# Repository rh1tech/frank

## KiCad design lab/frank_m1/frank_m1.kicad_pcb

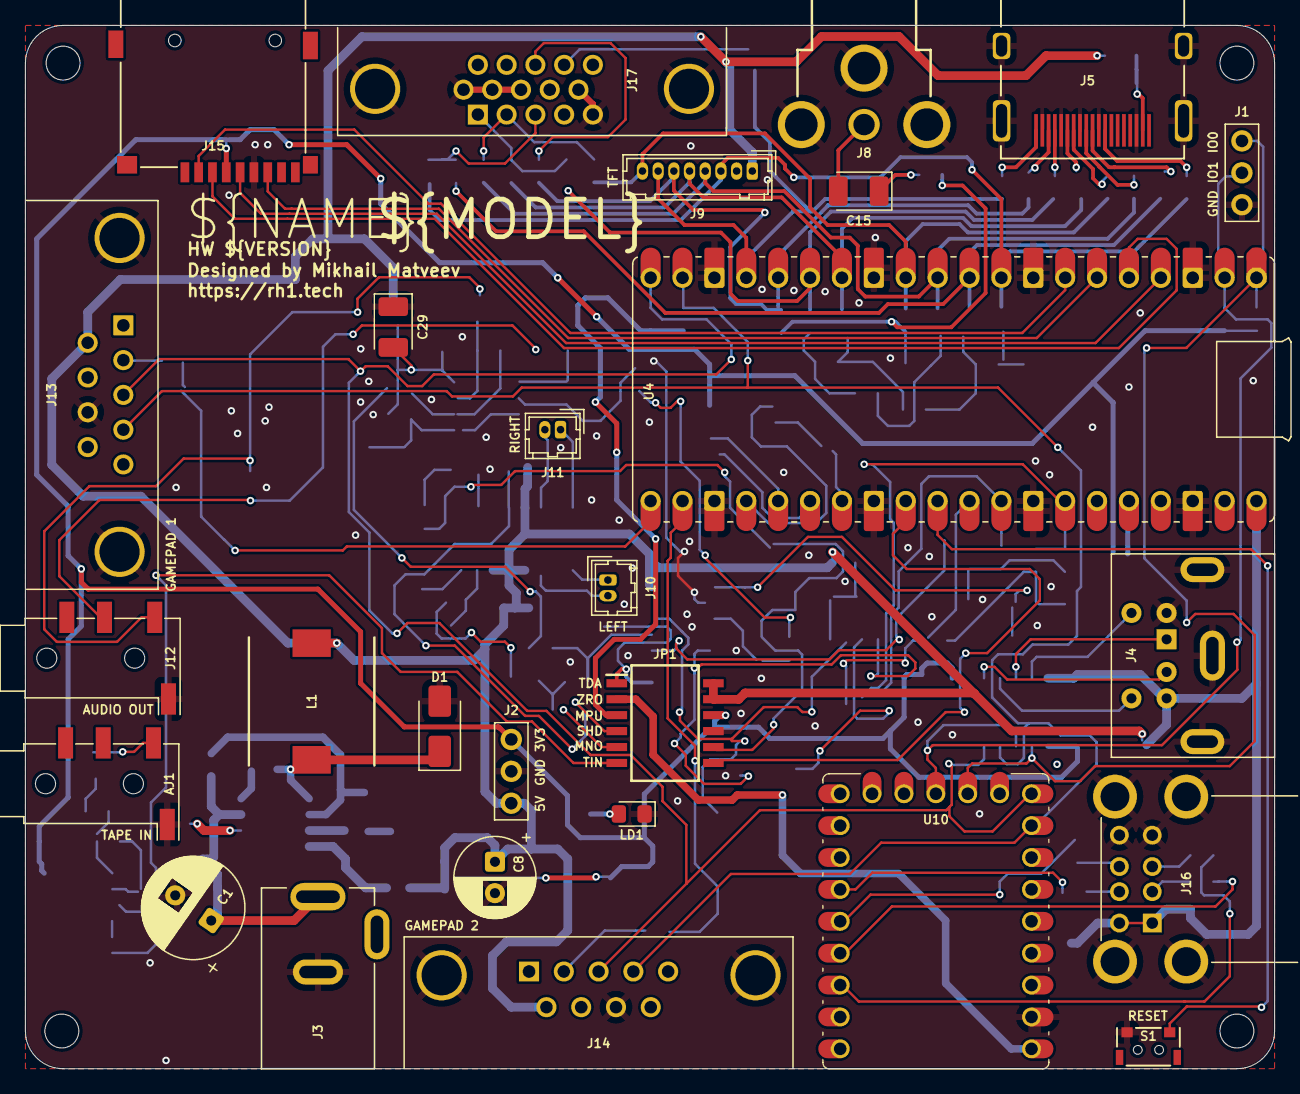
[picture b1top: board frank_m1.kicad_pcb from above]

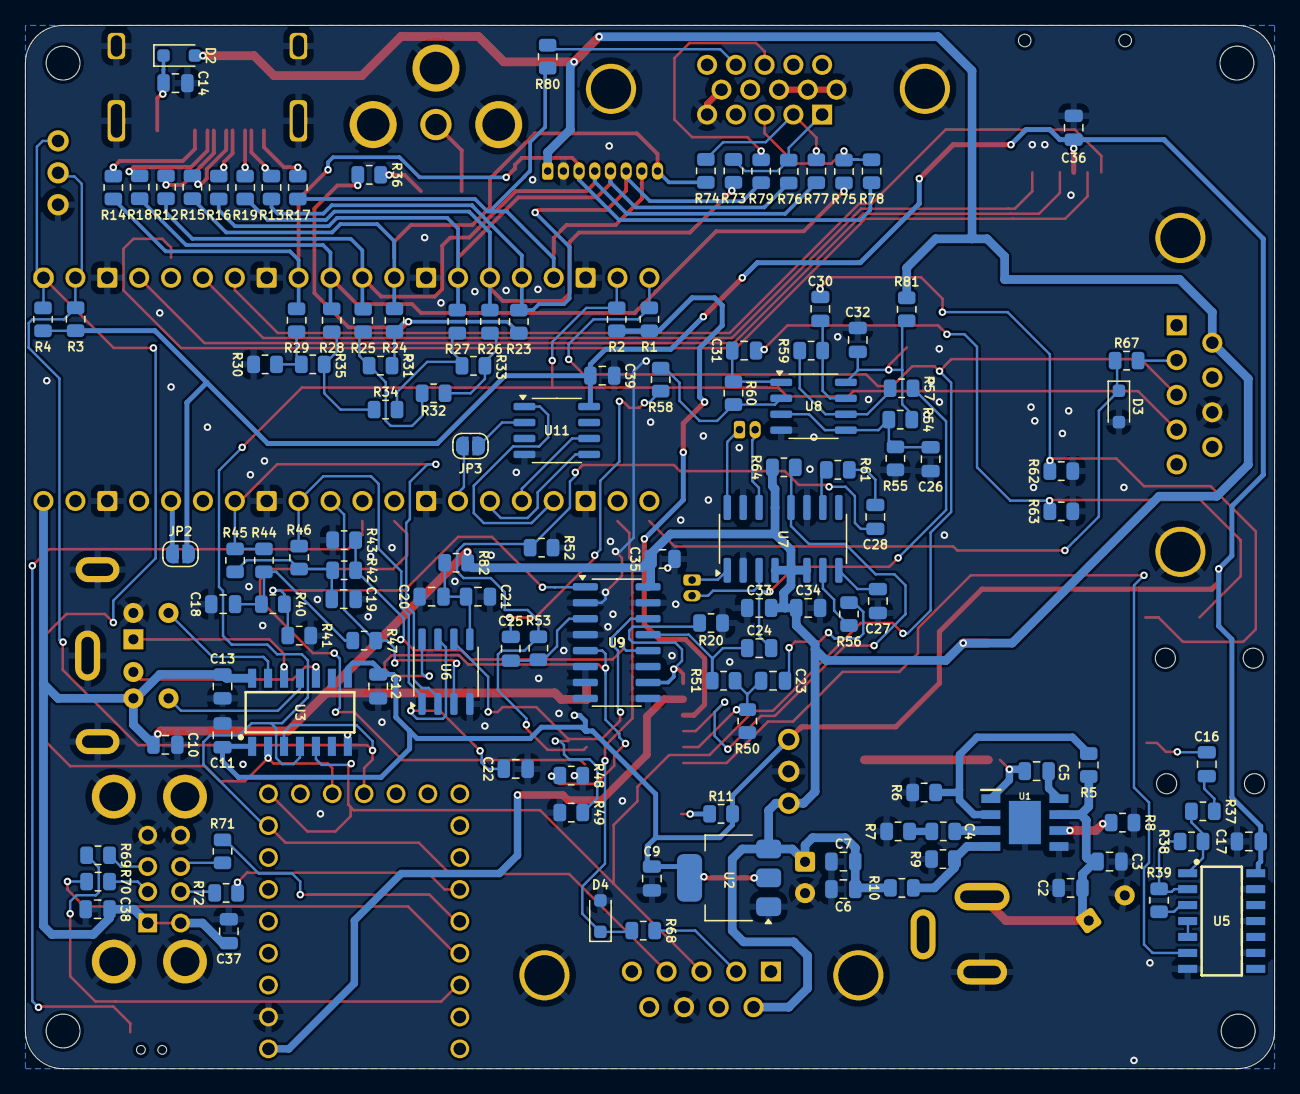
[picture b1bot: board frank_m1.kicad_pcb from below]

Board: 2 copper layers, 99.5 x 83.1 mm, 158 parts (127 on the bottom side), 119 nets.

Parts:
AJ1: PJ-320D; Jack (3.5mm, PJ-320D)
C1: 680u; Capacitor (Radial_D8.0mm_P3.50mm)
C2, C7, C9, C20, C22, C24, C25, C26, C30, C31, C37, C38: 10u; C_0805_2012Metric
C3, C5, C6, C10, C11, C12, C13, C14, C16, C17, C21, C27, C32, C35, C36, C39: 100n; C_0805_2012Metric
C4: 150pF; R_0805_2012Metric
C8: 220u; Capacitor (Radial_D6.3mm_P2.50mm)
C15: 220u; Capacitor (3528, tantalum, polar)
C18, C19: 47n; C_0805_2012Metric
C23, C28, C33: 1u; C_0805_2012Metric
C29: 10u; Capacitor (3528, tantalum, polar)
C34: 47u; C_0805_2012Metric
D1: 1N5822; D_SMA
D2: 1N5819WS; Diode (SOD-323)
D3, D4: 3V3; Diode (SOD-323)
H1, H2, H3, H4: Hole 2.7mm; Mounting Hole (2.7mm)
J1: UART; Pin Header (1x03)
J2: PWR; Pin Header (1x03)
J3: DC-005-5A-2.0; XKB_DC-005-5A-2.0
J4: MDC-036; MiniDIN (6 Pin, female)
J5: DC3RX19JA2; HDMI (female)
J8: RCA-103; RCJ-012
J9: Pin Header 1x08; Connector Female 1.25 JST 8P
J10: PAM L; Connector Female 1.25 JST 2P
J11: PAM R; Connector Female 1.25 JST 2P
J12: PJ-320D; Jack (3.5mm, PJ-320D)
J13, J14: D-SUB 9 Male; D-SUB (9 pin, male, top mount)
J15: 104031-0811; MicroSD (SMD, long)
J16: SS-52100-004; USB Type A (stacked)
J17: D-SUB 15 Female; D-SUB (15 pin, female)
JP1: Main Jumpers; SOIC127P830X260-12N
JP2, JP3: Jumper (Solder); Jumper (solder)
L1: 22uH; CDRH104RNP
LD1: Green; LED (0805)
R1, R2, R3, R4, R20, R40, R42, R51, R53, R54, R55, R56, R57, R58, R61, R64: 10K; R_0805_2012Metric
R5, R7, R8, R38, R39: 100K; R_0805_2012Metric
R6: 24K; R_0805_2012Metric
R9: 8.2K; R_0805_2012Metric
R10: 43K; R_0805_2012Metric
R11, R46, R47, R67, R68, R76, R77, R78: 1K; R_0805_2012Metric
R12, R13, R14, R15, R16, R17, R18, R19, R24, R25, R26, R27, R28, R29: 270R; R_0805_2012Metric
R23: 750R; R_0805_2012Metric
R30: 300R; R_0805_2012Metric
R31, R32, R33, R34, R35: 150R; R_0805_2012Metric
R36: 51R; R_0805_2012Metric
R37: 4.7K; R_0805_2012Metric
R41, R43, R44, R45, R50, R52: 2K; R_0805_2012Metric
R48, R49: 470R; R_0805_2012Metric
R59, R60: 47K; R_0805_2012Metric
R62, R63: 20K; R_0805_2012Metric
R69, R70, R71, R72: 22R; R_0805_2012Metric
R73, R74, R75: 330R; R_0805_2012Metric
R79, R80, R81, R82: 100R; R_0805_2012Metric
S1: Reset RP2530A; TACT-SIDE-4623
U1: MP1584EN-LF-Z; SOIC127P600X170-9N
U2: AMS1117 3.3; SOT-223
U3: TXS0104EDR; SOIC127P600X175-14N
U4: Rasberry Pi Pico; Raspberry Pi Pico
U5: CD4069UBM; SOIC127P600X175-14N
U6: TDA1387T; SO-8
U7: PAM8403D; SOP-16
U8: LM358; SO-8
U9: 74HC4052D; SOP-16
U10: RP2040-Zero; Raspberry Pi Zero
U11: ESP-PSRAM32; SO-8

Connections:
+3V3: C9.1, C11.1, C12.1, C17.1, C36.2, C39.1, J2.1, J15.4 (VDD), JP1.10, JP2.2 (B), R3.2, R4.2, R11.2, U2.2 (VO), U3.1 (VCCA), U3.8 (OE), U5.14 (VDD), U11.8 (VCC)
/AMP_L: C24.1, R51.1, U9.13 (1Z)
/AMP_OUT_L: C30.2, J12.T, R62.2
/AMP_OUT_R: C31.2, J12.R, R63.2
/AMP_R: C25.1, R53.1, U9.3 (2Z)
/AUDIOSW: JP1.1, R20.2, U9.10 (S0)
/Audio/AMP_PAM_OUTL_M: J10.2, U7.3 (-OUTL)
/Audio/AMP_PAM_OUTL_P: J10.1, U7.1 (+OUT_L)
/Audio/AMP_PAM_OUTR_M: J11.2, U7.14 (-OUT_R)
/Audio/AMP_PAM_OUTR_P: J11.1, U7.16 (+OUT_R)
/Composite/CVBS: C15.2, J8.1
/EN: R5.1, R6.1, U1.2 (EN)
/LOAD_IN: JP1.6, U5.6 (I=*C)
/MONO_L: C23.1, JP1.5, R50.1, R51.2
/MONO_R: C28.1, JP1.8, R52.1, R53.2
/MSPUP3V3: JP1.3, R1.2, R2.2
/PGPIO0: J1.1, R4.1, U3.2 (A1), U4.1 (GPIO0), U10.13 (12)
/PGPIO1: J1.2, R3.1, U3.3 (A2), U4.2 (GPIO1), U10.12 (11)
/PGPIO2: J15.5 (CLK), U4.4 (GPIO2)
/PGPIO3: J15.3 (CMD), U4.5 (GPIO3)
/PGPIO4: J15.7 (DAT0), U4.6 (GPIO4)
/PGPIO5: J15.2 (DAT3/CD), U4.7 (GPIO5)
/PGPIO6: J9.3, R14.2, R29.1, R78.1, U4.9 (GPIO6)
/PGPIO7: R18.2, R28.1, R75.1, U4.10 (GPIO7)
/PGPIO8: J9.4, R12.2, R25.1, R77.1, U4.11 (GPIO8)
/PGPIO9: J9.8, R15.2, R24.1, R74.1, U4.12 (GPIO9)
/PGPIO10: J9.5, R16.2, R27.1, R76.1, U4.14 (GPIO10)
/PGPIO11: R19.2, R26.1, R73.1, U4.15 (GPIO11)
/PGPIO12: J9.6, R13.2, R23.1, R79.2, U4.16 (GPIO12)
/PGPIO13: J9.7, R17.2, R80.2, U4.17 (GPIO13)
/PGPIO14: J13.4, J14.4, R2.1, U3.4 (A3), U4.19 (GPIO14), U10.16 (15)
/PGPIO15: J13.3, J14.3, R1.1, U3.5 (A4), U4.20 (GPIO15), U10.15 (14)
/PGPIO16: D3.1 (K), R67.1, U4.21 (GPIO16)
/PGPIO17: D4.1 (K), R68.1, U4.22 (GPIO17)
/PGPIO18: U4.24 (GPIO18), U11.1 (~CE)
/PGPIO19: U4.25 (GPIO19), U11.6 (SCLK)
/PGPIO20: U4.26 (GPIO20), U11.5 (SI/SIO)
/PGPIO21: JP3.2 (B), U4.27 (GPIO21)
/PGPIO22: JP1.7, U4.29 (GPIO22)
/PGPIO26: R47.2, U4.31 (GPIO26_ADC0), U6.3 (DATA)
/PGPIO27: R46.2, U4.32 (GPIO27_ADC1), U6.1 (SCLK)
/PGPIO28: R44.1, R45.1, U4.34 (GPIO28_ADC2), U6.2 (LRCK)
/PRUN: S1.1, U4.30 (RUN)
/PS2/KB_CLK_5V: J4.5, U3.13 (B1)
/PS2/KB_DATA_5V: J4.1, U3.12 (B2)
/PS2/MS_CLK_5V: J4.6, U3.11 (B3)
/PS2/MS_DATA_5V: J4.2, U3.10 (B4)
/PWM_L: R42.2, R43.1, U9.12 (1Y0)
/PWM_R: R40.2, R41.1, U9.1 (2Y0)
/Power/VBUS_IN: C1.1, C2.1, C3.1, J3.1, R5.2, U1.7 (VIN)
/SHND: JP1.4, R64.2, U7.12 (SHND)
/TDA_L: R49.2, U6.6 (A_LEFT), U9.14 (1Y1)
/TDA_R: R48.1, U6.8 (A_RIGHT), U9.5 (2Y1)
/Tape In/TAPE: AJ1.T, C16.2
/ZGPIO2: R69.1, U10.3 (2)
/ZGPIO3: R70.1, U10.4 (3)
/ZGPIO4: R71.1, U10.5 (4)
/ZGPIO5: R72.1, U10.6 (5)
/Z_VBUS: JP1.2, U10.23 (5V)
GND: AJ1.S, C1.2, C2.2, C3.2, C6.1, C7.2, C8.2, C9.2, C10.2, C11.2, C12.2, C13.2, C14.2, C17.2, C18.2, C19.2, C20.2, C21.2, C22.2, C26.1, C27.2, C29.1, C32.1, C33.2, C34.2, C35.1, C36.1, C37.2, C38.2, C39.2, D1.2 (A), D3.2 (A), D4.2 (A), J1.3, J2.2, J3.2, J4.3, J5.2 (G_D2), J5.5 (G_D1), J5.8 (G_D0), J5.11 (G_CLK), J5.17 (G_DDC/CEC), J5.20 (SHIELD1), J5.21 (SHIELD2), J5.22 (SHIELD3), J5.23 (SHIELD4), J8.2, J9.2, J12.S, J13.8, J14.8, J15.6 (VSS), J16.4 (GND1), J16.8 (GND2), J16.9 (Shield), J17.0, J17.5, J17.6, J17.7, J17.8, J17.10, JP1.9, LD1.1 (K), R6.2, R7.2, R8.2, R9.1, R20.1, R30.1, R41.2, R43.2, R48.2, R49.1, R50.2, R52.2, R55.1, R62.1, R63.1, S1.2, U1.5 (GND), U1.9 (EP), U2.1 (GND), U3.7 (GND), U4.3 (GND), U4.8 (GND), U4.13 (GND), U4.18 (GND), U4.23 (GND), U4.28 (GND), U4.33 (AGND), U4.38 (GND), U5.7 (VSS), U5.9 (D14), U5.11 (E), U5.13 (F), U6.4 (AGND), U7.2 (PGND), U7.11 (GND), U7.15 (PGND), U8.4 (V-), U9.2 (2Y2), U9.4 (2Y3), U9.6 (~E), U9.7 (VEE), U9.8 (GND), U9.9 (S1), U9.11 (1Y3), U9.15 (1Y2), U10.22 (GND), U11.4 (VSS)
unnamed: C4.2, R7.1
unnamed: C15.1, R36.2
unnamed: C16.1, R37.2
unnamed: C18.1, R40.1, R44.2, R47.1
unnamed: C19.1, R42.1, R45.2, R46.1
unnamed: C23.2, R56.2
unnamed: C24.2, R57.2
unnamed: C25.2, R58.2
unnamed: C28.2, R61.2
unnamed: C30.1, R59.1, U8.7
unnamed: C31.1, R60.1, U8.1
unnamed: C5.2, D1.1 (K), L1.1, U1.1 (SW)
unnamed: C14.1, D2.1 (K), J5.18 (+5V)
unnamed: J5.12 (CLKN), R14.1
unnamed: J5.10 (CLKP), R18.1
unnamed: J5.9 (D0N), R12.1
unnamed: J5.7 (D0P), R15.1
unnamed: J5.6 (D1N), R16.1
unnamed: J5.4 (D1P), R19.1
unnamed: J5.3 (D2N), R13.1
unnamed: J5.1 (D2P), R17.1
unnamed: J13.2, R67.2
unnamed: J14.2, R68.2
unnamed: J16.3 (D1+), R69.2
unnamed: J16.2 (D1-), R70.2
unnamed: J16.7 (D2+), R71.2
unnamed: J16.6 (D2-), R72.2
unnamed: J17.1, R73.2, R76.2
unnamed: J17.2, R74.2, R77.2
unnamed: J17.3, R75.2, R78.2
unnamed: J17.13, R79.1
unnamed: J17.14, R80.1
unnamed: JP2.1 (A), U4.36 (3V3)
unnamed: JP3.1 (A), U11.2 (SO/SIO)
unnamed: LD1.2 (A), R11.1
unnamed: R23.2, R24.2, R31.2, R36.1
unnamed: R25.2, R31.1, R32.2
unnamed: R26.2, R32.1, R33.2
unnamed: R27.2, R33.1, R34.2
unnamed: R28.2, R34.1, R35.2
unnamed: R29.2, R30.2, R35.1
unnamed: C5.1, U1.8 (BST)
unnamed: C4.1, U1.3 (COMP)
unnamed: R9.2, R10.2, U1.4 (FB)
unnamed: R8.1, U1.6 (FREQ)
unnamed: R37.1, R38.2, U5.1 (A)
unnamed: R39.1, U5.3 (B)
unnamed: U5.4 (H=*B), U5.5 (C)
unnamed: R38.1, R39.2, U5.2 (G-*A)
unnamed: C22.1, U6.7 (FLT)
unnamed: C20.1, C21.1, R82.1, U6.5 (VA)
unnamed: R56.1, U7.7 (INL)
unnamed: R61.1, U7.10 (INR)
unnamed: C27.1, U7.8 (VREF)
unnamed: C26.2, R54.1, R55.2, U8.3 (+), U8.5 (+)
unnamed: R58.1, R60.2, U8.2 (-)
unnamed: R57.1, R59.2, U8.6 (-)
unnamed: C29.2, C32.2, R54.2, R81.2, U8.8 (V+)
VBUS: C6.2, C7.1, C8.1, C10.1, C13.1, C33.1, C34.1, C35.2, C37.1, C38.1, D2.2 (A), J2.3, J4.4, J9.1, J13.6, J14.6, J16.1 (VBUS1), J16.5 (VBUS2), JP1.11, JP1.12, L1.2, R10.1, R64.1, R81.1, R82.2, U2.3 (VI), U3.14 (VCCB), U4.40 (VBUS), U7.4 (PVDD), U7.5 (MUTE), U7.6 (VDD), U7.13 (PVDD), U9.16 (VCC)

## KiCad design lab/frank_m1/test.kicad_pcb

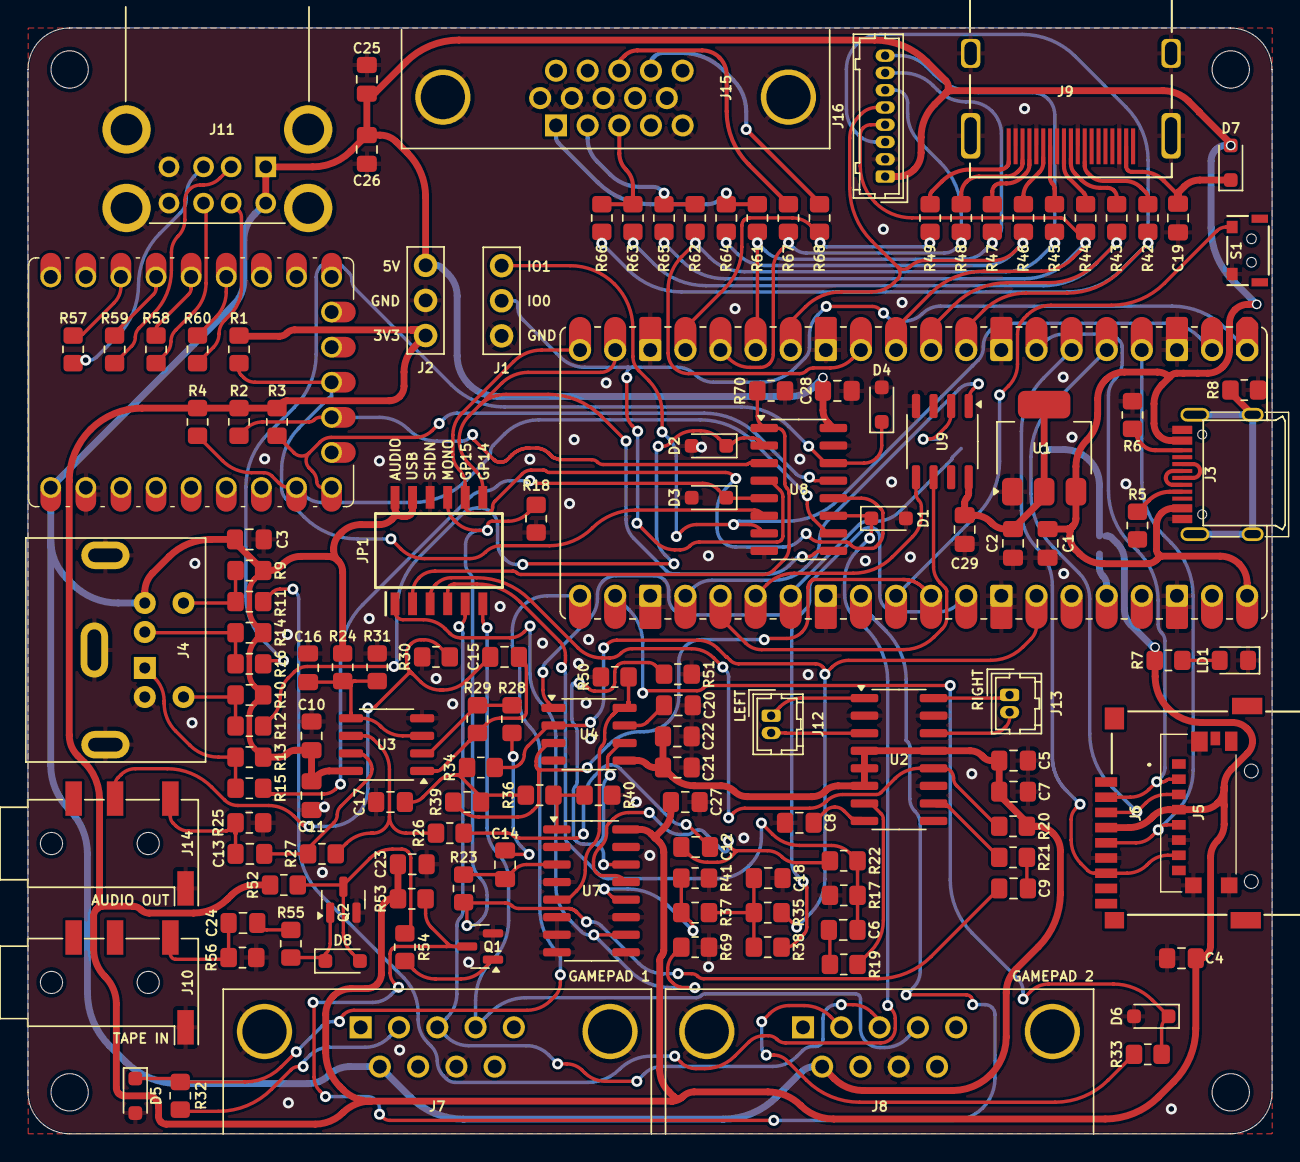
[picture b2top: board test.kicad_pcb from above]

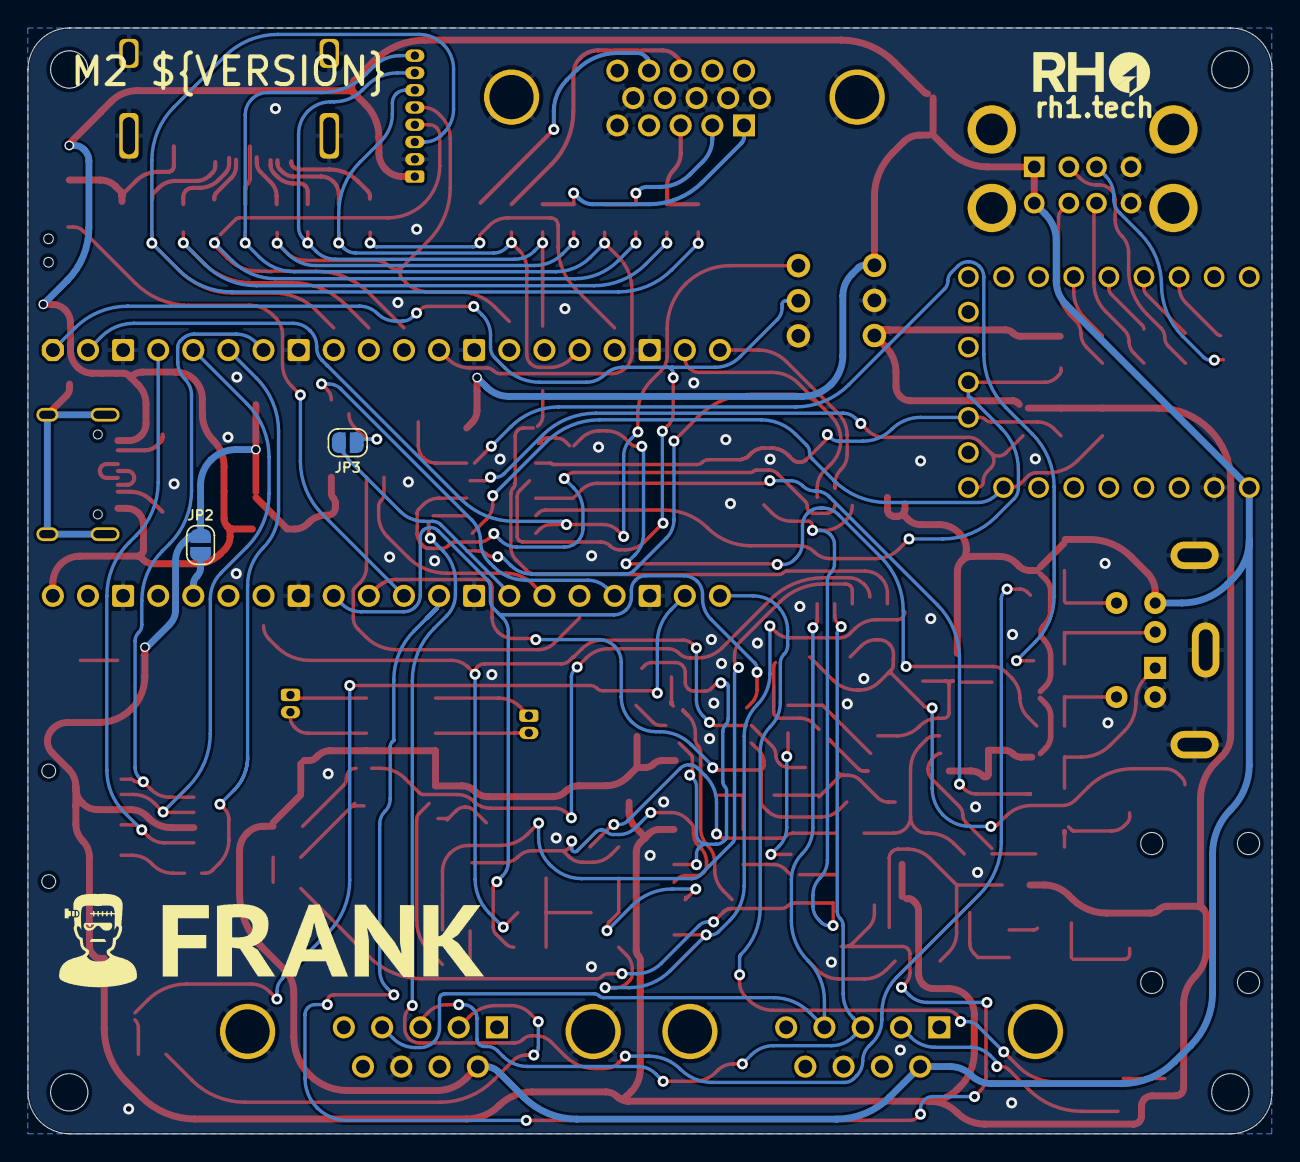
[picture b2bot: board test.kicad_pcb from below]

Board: 2 copper layers, 90.0 x 80.0 mm, 143 parts (2 on the bottom side), 113 nets.

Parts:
C1, C2, C10, C12, C13, C14, C15, C16, C20, C21, C25, C26: 10u; Capacitor (0805)
C3, C4, C8, C11, C19, C22, C23, C24, C27, C28, C29: 100n; Capacitor (0805)
C5, C6, C9: 1u; Capacitor (0805)
C7: 47u; Capacitor (0805)
C17, C18: 47n; Capacitor (0805)
D1, D2, D3, D4, D5, D6: 3V3; Diode (SOD-323)
D7: 1N5819WS; Diode (SOD-323)
D8: 1N4148; Diode (SOD-323)
H1, H2, H3, H4: Hole 2.7mm; Mounting Hole (2.7mm)
J1, J2: Pin Header 1x03; Pin Header (1x03)
J3: USB4215; USB Type C
J4: MDC-036; MiniDIN (6 Pin, female)
J5: 0475710001; MicroSD (SMD, short)
J6: 104031-0811; MicroSD (SMD, long)
J7, J8: D-SUB 9 Male; D-SUB (9 pin, male, top mount)
J9: DC3RX19JA2; HDMI (female)
J10, J14: PJ-320D; Jack (3.5mm, PJ-320D)
J11: SS-52100-004; USB Type A (stacked)
J12: PAM L; Connector Female 1.25 JST 2P
J13: PAM R; Connector Female 1.25 JST 2P
J15: D-SUB 15 Female; D-SUB (15 pin, female)
J16: Pin Header 1x08; Connector Female 1.25 JST 8P
JP1: Main Jumpers; SOIC127P830X260-12N
JP2, JP3: Jumper (Solder); Jumper (solder)
LD1: Green; LED (0805)
Q1, Q2: BC850; SOT-23
R1, R2, R3, R4, R19, R20, R21, R22, R23, R24, R26, R28, R31, R36, R37, R52, R54, R55, R69, R70: 10K; Resistor (0805)
R5, R6: 5.1K; Resistor (0805)
R7, R9, R10, R13, R14, R32, R33, R38, R39, R53, R64, R65, R66: 1K; Resistor (0805)
R8: 1M; Resistor (0805)
R11, R12, R15, R16, R56, R67, R68: 100R; Resistor (0805)
R17, R18, R34, R35, R40, R41: 2K; Resistor (0805)
R25, R30: 20K; Resistor (0805)
R27, R29: 47K; Resistor (0805)
R42, R43, R44, R45, R46, R47, R48, R49: 270R; Resistor (0805)
R50, R51: 470R; Resistor (0805)
R57, R58, R59, R60: 22R; Resistor (0805)
R61, R62, R63: 330R; Resistor (0805)
S1: Reset RP2530A; TACT-SIDE-4623
U1: NCP1117 3.3; SOT-223
U2: PAM8403D; SOP-16
U3: LM358; SO-8
U4: TDA1387T; SO-8
U5: Rasberry Pi Pico; Raspberry Pi Pico
U6: RP2040-Zero; Raspberry Pi Zero
U7: 74HC4052D; SOP-16
U8: SN74CBT3257CDR; SOP-16
U9: ESP-PSRAM32; SO-8

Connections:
+3V3: C2.1, C4.2, C23.1, C27.2, C29.1, J2.1, J5.P4 (VDD), J6.4 (VDD), JP2.2 (B), R1.2, R2.2, R3.2, R4.2, R7.2, R52.1, R53.1, U1.2 (VO), U7.16 (VCC), U9.8 (VCC)
/AMP_L: C12.1, R22.1, U7.13 (1Z)
/AMP_R: C14.1, R23.1, U7.3 (2Z)
/ASW: JP1.1, R69.2, U7.10 (S0)
/Audio/AMP_OUTL: C13.2, J14.T, R25.2
/Audio/AMP_OUTR: C15.2, J14.R, R30.2
/Audio/AMP_PAM_OUTL_M: J12.2, U2.3 (-OUTL)
/Audio/AMP_PAM_OUTL_P: J12.1, U2.1 (+OUT_L)
/Audio/AMP_PAM_OUTR_M: J13.2, U2.14 (-OUT_R)
/Audio/AMP_PAM_OUTR_P: J13.1, U2.16 (+OUT_R)
/GAMEPAD_J3: J7.3, J8.3, JP1.5
/GAMEPAD_J4: J7.4, J8.4, JP1.6
/MONO_L: C6.1, JP1.4, R17.1, R22.2
/MONO_R: C9.1, JP1.9, R18.1, R23.2
/PGPIO0: J1.2, U5.1 (GPIO0), U8.4 (1A)
/PGPIO1: J1.3, U5.2 (GPIO1), U8.7 (2A)
/PGPIO2: J5.P5 (CLK), J6.5 (CLK), U5.4 (GPIO2)
/PGPIO3: J5.P3 (CMD), J6.3 (CMD), U5.5 (GPIO3)
/PGPIO4: J5.P7 (DAT0), J6.7 (DAT0), U5.6 (GPIO4)
/PGPIO5: J5.P2 (CD/DAT3), J6.2 (DAT3/CD), U5.7 (GPIO5)
/PGPIO6: J16.3, R42.2, R66.1, U5.9 (GPIO6)
/PGPIO7: R43.2, R63.1, U5.10 (GPIO7)
/PGPIO8: J16.4, R44.2, R65.1, U5.11 (GPIO8)
/PGPIO9: J16.8, R45.2, R62.1, U5.12 (GPIO9)
/PGPIO10: J16.5, R46.2, R64.1, U5.14 (GPIO10)
/PGPIO11: J16.7, R47.2, R61.1, U5.15 (GPIO11)
/PGPIO12: J16.6, R48.2, R67.2, U5.16 (GPIO12)
/PGPIO13: R49.2, R68.2, U5.17 (GPIO13)
/PGPIO14: JP1.7, U5.19 (GPIO14), U8.9 (3A)
/PGPIO15: JP1.8, U5.20 (GPIO15), U8.12 (4A)
/PGPIO16: D5.1 (K), R32.1, U5.21 (GPIO16)
/PGPIO17: D6.1 (K), R33.1, U5.22 (GPIO17)
/PGPIO18: U5.24 (GPIO18), U9.1 (~CE)
/PGPIO19: U5.25 (GPIO19), U9.6 (SCLK)
/PGPIO20: U5.26 (GPIO20), U9.5 (SI/SIO)
/PGPIO21: JP3.2 (B), U5.27 (GPIO21)
/PGPIO22: Q1.3 (C), R53.2, U5.29 (GPIO22)
/PGPIO26: R39.2, U4.3 (DATA), U5.31 (GPIO26_ADC0)
/PGPIO27: R38.2, U4.1 (SCLK), U5.32 (GPIO27_ADC1)
/PGPIO28: R34.1, R35.1, U4.2 (LRCK), U5.34 (GPIO28_ADC2)
/PRUN: S1.1, U5.30 (RUN)
/PS2/PS2_KB_CLK: J4.5, R10.1, R12.1
/PS2/PS2_KB_DATA: J4.1, R13.1, R15.1
/PS2/PS2_MS_CLK: J4.6, R9.1, R11.1
/PS2/PS2_MS_DATA: J4.2, R14.1, R16.1
/PS2_K_CLK: D2.1 (K), R12.2, U8.2 (1B1)
/PS2_K_DATA: D3.1 (K), R15.2, U8.5 (2B1)
/PS2_M_CLK: D1.1 (K), R11.2, U8.11 (3B1)
/PS2_M_DATA: D4.1 (K), R16.2, U8.14 (4B1)
/PSW: JP1.2, R70.2, U8.1 (S)
/PWM_L: R37.2, R41.1, U7.12 (1Y0)
/PWM_R: R36.2, R40.1, U7.1 (2Y0)
/Power/D+: J3.6 (DP1), J3.8 (DP2)
/Power/D-: J3.5 (DN2), J3.7 (DN1)
/SHND: JP1.3, R20.2, U2.12 (SHND)
/TDA_L: R51.2, U4.6 (A_LEFT), U7.14 (1Y1)
/TDA_R: R50.1, U4.8 (A_RIGHT), U7.5 (2Y1)
/ZGPIO2: R57.1, U6.3 (2)
/ZGPIO3: R59.1, U6.4 (3)
/ZGPIO4: R58.1, U6.5 (4)
/ZGPIO5: R60.1, U6.6 (5)
/ZGPIO11: R1.1, U6.12 (11), U8.6 (2B2)
/ZGPIO12: R2.1, U6.13 (12), U8.3 (1B2)
/ZGPIO14: R3.1, U6.15 (14), U8.13 (4B2)
/ZGPIO15: R4.1, U6.16 (15), U8.10 (3B2)
GND: C1.2, C2.2, C3.2, C4.1, C5.2, C7.2, C8.2, C10.1, C11.1, C16.1, C17.2, C18.2, C19.2, C20.2, C21.2, C22.2, C23.2, C25.2, C26.2, C27.1, C28.1, C29.2, D1.2 (A), D2.2 (A), D3.2 (A), D4.2 (A), D5.2 (A), D6.2 (A), J1.1, J2.2, J3.1 (GND), J3.12 (GND), J4.3, J5.G1 (GND_1), J5.G2 (GND_2), J5.G3 (GND_3), J5.P6 (VSS), J6.6 (VSS), J7.8, J8.8, J9.2 (G_D2), J9.5 (G_D1), J9.8 (G_D0), J9.11 (G_CLK), J9.17 (G_DDC/CEC), J9.20 (SHIELD1), J9.21 (SHIELD2), J9.22 (SHIELD3), J9.23 (SHIELD4), J10.S, J11.4 (GND1), J11.8 (GND2), J11.9 (Shield), J14.S, J15.0, J15.5, J15.6, J15.7, J15.8, J15.10, J16.2, JP1.10, LD1.1 (K), Q1.2 (E), Q2.2 (E), R5.1, R6.1, R8.2, R17.2, R18.2, R25.1, R30.1, R31.1, R40.2, R41.2, R50.2, R51.1, R56.2, R69.1, R70.1, S1.2, U1.1 (GND), U2.2 (PGND), U2.11 (GND), U2.15 (PGND), U3.4 (V-), U4.4 (AGND), U5.3 (GND), U5.8 (GND), U5.13 (GND), U5.18 (GND), U5.23 (GND), U5.28 (GND), U5.33 (AGND), U5.38 (GND), U6.22 (GND), U7.2 (2Y2), U7.4 (2Y3), U7.6 (~E), U7.7 (VEE), U7.8 (GND), U7.9 (S1), U7.11 (1Y3), U7.15 (1Y2), U8.8 (GND), U8.15 (~OE), U9.4 (VSS)
unnamed: C6.2, R19.2
unnamed: C9.2, R21.2
unnamed: C12.2, R26.2
unnamed: C13.1, R27.1, U3.7
unnamed: C14.2, R28.2
unnamed: C15.1, R29.1, U3.1
unnamed: C17.1, R34.2, R36.1, R39.1
unnamed: C18.1, R35.2, R37.1, R38.1
unnamed: C24.1, J10.T, R56.1
unnamed: C24.2, R55.1
unnamed: C19.1, D7.1 (K), J9.18 (+5V)
unnamed: D8.2 (A), Q2.3 (C), R52.2, R54.1
unnamed: D8.1 (K), Q2.1 (B), R55.2
unnamed: J3.4 (CC1), R5.2
unnamed: J3.10 (CC2), R6.2
unnamed: J3.13 (SHIELD), R8.1
unnamed: J7.2, R32.2
unnamed: J8.2, R33.2
unnamed: J9.12 (CLKN), R42.1
unnamed: J9.10 (CLKP), R43.1
unnamed: J9.9 (D0N), R44.1
unnamed: J9.7 (D0P), R45.1
unnamed: J9.6 (D1N), R46.1
unnamed: J9.4 (D1P), R47.1
unnamed: J9.3 (D2N), R48.1
unnamed: J9.1 (D2P), R49.1
unnamed: J11.3 (D1+), R57.2
unnamed: J11.2 (D1-), R59.2
unnamed: J11.7 (D2+), R58.2
unnamed: J11.6 (D2-), R60.2
unnamed: J15.1, R61.2, R64.2
unnamed: J15.2, R62.2, R65.2
unnamed: J15.3, R63.2, R66.2
unnamed: J15.13, R67.1
unnamed: J15.14, R68.1
unnamed: JP2.1 (A), U5.36 (3V3)
unnamed: JP3.1 (A), U9.2 (SO/SIO)
unnamed: LD1.2 (A), R7.1
unnamed: Q1.1 (B), R54.2
unnamed: R19.1, U2.7 (INL)
unnamed: R21.1, U2.10 (INR)
unnamed: C8.1, U2.8 (VREF)
unnamed: C16.2, R24.1, R31.2, U3.3 (+), U3.5 (+)
unnamed: R28.1, R29.2, U3.2 (-)
unnamed: R26.1, R27.2, U3.6 (-)
unnamed: C20.1, U4.7 (FLT)
VBUS: C1.1, C3.1, C5.1, C7.1, C10.2, C11.2, C21.1, C22.1, C25.1, C26.1, C28.2, D7.2 (A), J2.3, J3.2 (VBUS), J3.11 (VBUS), J4.4, J7.6, J8.6, J11.1 (VBUS1), J11.5 (VBUS2), J16.1, JP1.11, JP1.12, R9.2, R10.2, R13.2, R14.2, R20.1, R24.2, U1.3 (VI), U2.4 (PVDD), U2.5 (MUTE), U2.6 (VDD), U2.13 (PVDD), U3.8 (V+), U4.5 (VA), U5.40 (VBUS), U6.23 (5V), U8.16 (VCC)

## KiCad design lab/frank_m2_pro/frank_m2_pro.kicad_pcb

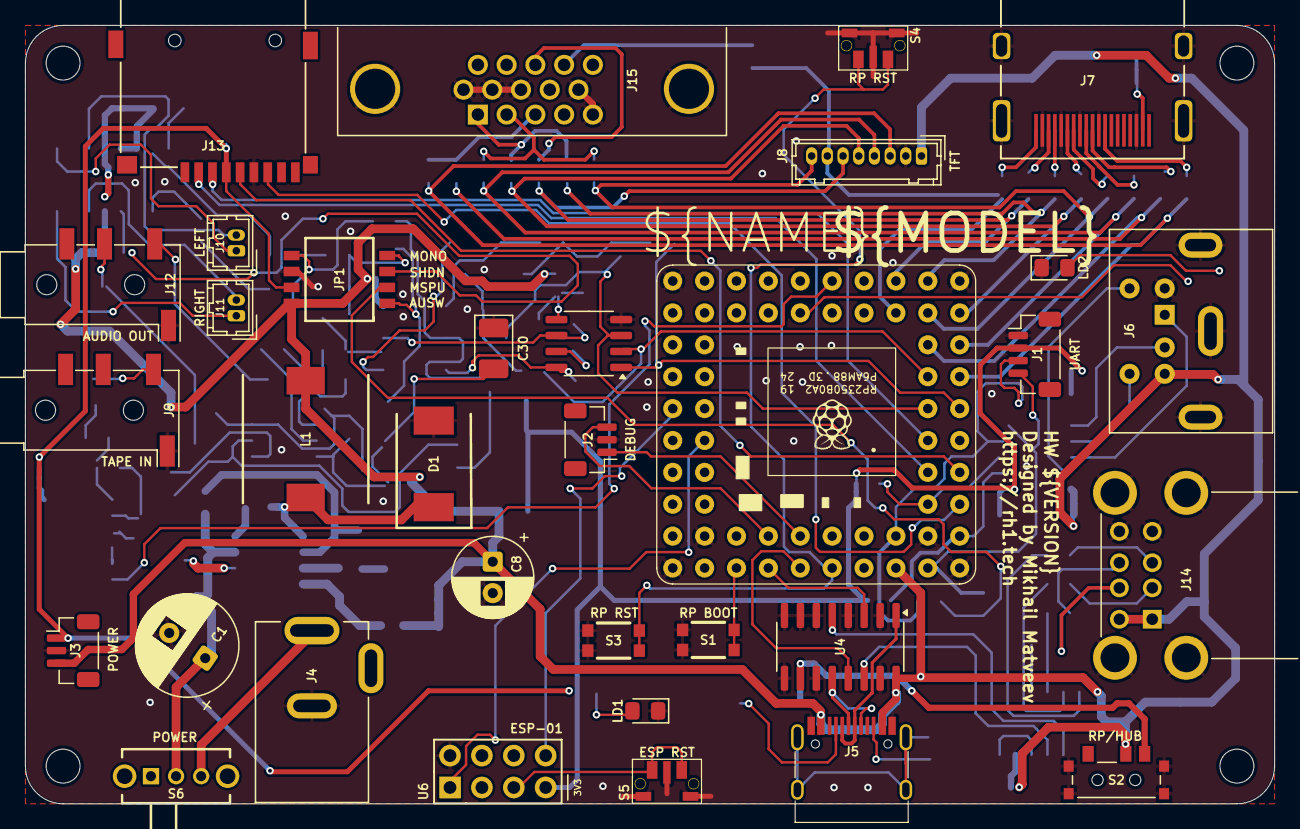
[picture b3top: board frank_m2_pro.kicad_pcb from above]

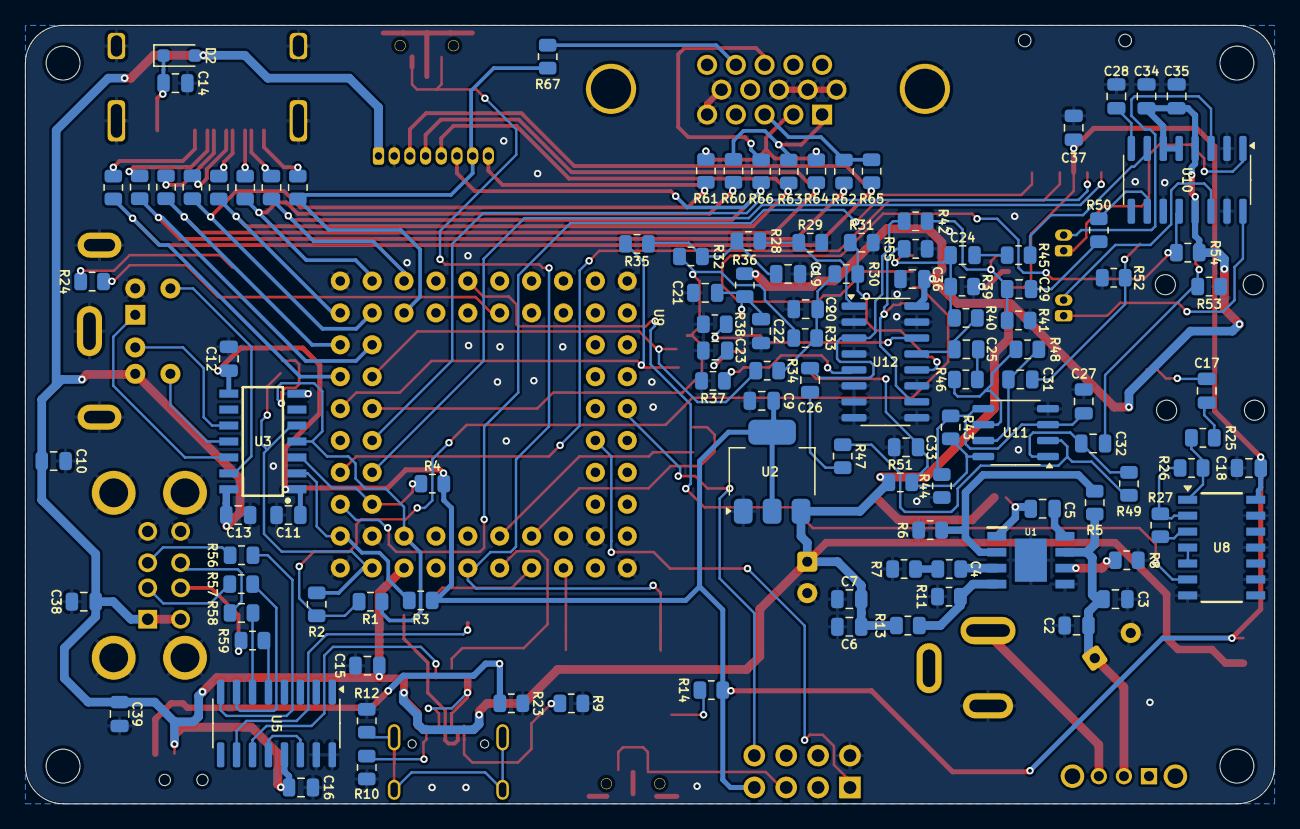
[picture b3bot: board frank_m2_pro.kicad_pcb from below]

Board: 2 copper layers, 99.5 x 62.0 mm, 149 parts (112 on the bottom side), 119 nets.

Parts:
C1: 680u; Capacitor (Radial_D8.0mm_P3.50mm)
C2, C7, C9, C21, C23, C25, C26, C27, C31, C32, C38, C39: 10u; C_0805_2012Metric
C3, C5, C6, C10, C11, C12, C13, C14, C15, C17, C18, C22, C28, C33, C36, C37: 100n; C_0805_2012Metric
C4: 150pF; R_0805_2012Metric
C8: 220u; Capacitor (Radial_D6.3mm_P2.50mm)
C16: 4.7u; C_0805_2012Metric
C19, C20: 47n; C_0805_2012Metric
C24, C29, C34: 1u; C_0805_2012Metric
C30: 10u; Capacitor (3528, tantalum, polar)
C35: 47u; C_0805_2012Metric
D1: 1N5822; SS34
D2: 1N5819WS; Diode (SOD-323)
H1, H2, H3, H4: Hole 2.7mm; Mounting Hole (2.7mm)
J1: UART; JST_SH_BM04B-SRSS-TB_1x04-1MP_P1.00mm_Vertical
J2: DEBUG; JST_SH_BM03B-SRSS-TB_1x03-1MP_P1.00mm_Vertical
J3: PWR; JST_SH_BM03B-SRSS-TB_1x03-1MP_P1.00mm_Vertical
J4: DC-005-5A-2.0; XKB_DC-005-5A-2.0
J5: USB4215-03-A; USB Type C
J6: MDC-036; MiniDIN (6 Pin, female)
J7: DC3RX19JA2; HDMI (female)
J8: Pin Header 1x08; Connector Female 1.25 JST 8P
J9, J12: PJ-320D; Jack (3.5mm, PJ-320D)
J10: PAM L; Connector Female 1.25 JST 2P
J11: PAM R; Connector Female 1.25 JST 2P
J13: 104031-0811; MicroSD (SMD, long)
J14: SS-52100-004; USB Type A (stacked)
J15: VGA; D-SUB (15 pin, female)
JP1: Config Switches; CHS04TB1
L1: 22uH; CDRH104RNP
LD1: Green; LED (0805)
LD2: Blue; LED (0805)
R1, R2, R3, R4, R23, R28, R30, R40, R42, R43, R44, R45, R46, R47, R50, R54, R55: 10K; R_0805_2012Metric
R5, R7, R8, R26, R27: 100K; R_0805_2012Metric
R6: 24K; R_0805_2012Metric
R9, R10: 5.1K; R_0805_2012Metric
R11: 8.2K; R_0805_2012Metric
R12: 1M; R_0805_2012Metric
R13: 43K; R_0805_2012Metric
R14, R24, R34, R35, R63, R64, R65: 1K; R_0805_2012Metric
R15, R16, R17, R18, R19, R20, R21, R22: 270R; R_0805_2012Metric
R25: 4.7K; R_0805_2012Metric
R29, R31, R32, R33, R39, R41: 2K; R_0805_2012Metric
R36, R51, R66, R67: 100R; R_0805_2012Metric
R37, R38: 470R; R_0805_2012Metric
R48, R49: 47K; R_0805_2012Metric
R52, R53: 20K; R_0805_2012Metric
R56, R57, R58, R59: 22R; R_0805_2012Metric
R60, R61, R62: 330R; R_0805_2012Metric
S1: Bootselect; KMR_2
S2: MSK12C02; SW_MSK12C02
S3: RP Reset; KMR_2
S4: RP Reset; TS-1234VW
S5: ESP Reset; TS-1234VW
S6: SK12D07VG3NS
U1: MP1584EN-LF-Z; SOIC127P600X170-9N
U2: AMS1117 3.3; SOT-223
U3: TXS0104EDR; SOIC127P600X175-14N
U4, U12: 74HC4052D; SOP-16
U5: MW7211A; SOP-16
U6: ESP-01v090; ESP-01
U7: Pimoroni PGA2350; PGA2350
U8: CD4069UBM; SOIC127P600X175-14N
U9: TDA1387T; SO-8
U10: PAM8403D; SOP-16
U11: LM358; SO-8

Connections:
+3V3: C9.1, C11.1, C12.1, C18.1, C37.2, J1.2, J3.1, J13.4 (VDD), JP1.7, R3.2, R4.2, R14.2, U2.2 (VO), U3.1 (VCCA), U3.8 (OE), U6.7 (VCC), U8.14 (VDD)
/AMP_L: C25.1, R40.1, U12.13 (1Z)
/AMP_OUT_L: C31.2, J12.T, R52.2
/AMP_OUT_R: C32.2, J12.R, R53.2
/AMP_R: C26.1, R42.1, U12.3 (2Z)
/AUDIOSW: JP1.1, R55.2, U12.10 (S0)
/Audio/AMP_PAM_OUTL_M: J10.2, U10.3 (-OUTL)
/Audio/AMP_PAM_OUTL_P: J10.1, U10.1 (+OUT_L)
/Audio/AMP_PAM_OUTR_M: J11.2, U10.14 (-OUT_R)
/Audio/AMP_PAM_OUTR_P: J11.1, U10.16 (+OUT_R)
/BOOTSEL: S1.1, S1.2, U7.51 (BOOTSEL)
/ERST: S5.1, U6.5 (RST)
/HDM: U4.5 (2Y1), U5.10 (DMU)
/HDP: U4.14 (1Y1), U5.11 (DPU)
/MONO_L: C24.1, JP1.4, R39.1, R40.2
/MONO_R: C29.1, JP1.5, R41.1, R42.2
/MSPUP3V3: JP1.2, R1.2, R2.2
/PDM: U4.3 (2Z), U7.53 (USB_DM)
/PDP: U4.13 (1Z), U7.54 (USB_DP)
/PGPIO0: J1.3, R1.1, U3.4 (A3), U7.61 (GP0)
/PGPIO1: J1.4, R2.1, U3.5 (A4), U7.62 (GP1)
/PGPIO2: R3.1, U3.2 (A1), U7.2 (GP2)
/PGPIO3: R4.1, U3.3 (A2), U7.3 (GP3)
/PGPIO4: J13.7 (DAT0), U7.4 (GP4)
/PGPIO5: J13.2 (DAT3/CD), U7.5 (GP5)
/PGPIO6: J13.5 (CLK), U7.6 (GP6)
/PGPIO7: J13.3 (CMD), U7.7 (GP7)
/PGPIO9: R32.1, R33.1, U7.9 (GP9), U9.3 (DATA)
/PGPIO10: R35.2, U7.10 (GP10), U9.1 (SCLK)
/PGPIO11: R34.2, U7.11 (GP11), U9.2 (LRCK)
/PGPIO12: J8.3, R17.2, R65.1, U7.12 (GP12)
/PGPIO13: R21.2, R62.1, U7.13 (GP13)
/PGPIO14: J8.4, R15.2, R64.1, U7.14 (GP14)
/PGPIO15: J8.8, R18.2, R61.1, U7.15 (GP15)
/PGPIO16: J8.5, R19.2, R63.1, U7.16 (GP16)
/PGPIO17: R22.2, R60.1, U7.17 (GP17)
/PGPIO18: J8.6, R16.2, R66.2, U7.19 (GP18)
/PGPIO19: J8.7, R20.2, R67.2, U7.20 (GP19)
/PGPIO22: U7.23 (GP22), U8.6 (I=*C)
/PGPIO38: U6.8 (URXD), U7.40 (GP38)
/PGPIO39: U6.1 (UTXD), U7.41 (GP39)
/PRUN: S3.1, S3.2, S4.1, U7.56 (RUN)
/PS2/KB_CLK_5V: J6.5, U3.13 (B1)
/PS2/KB_DATA_5V: J6.1, U3.12 (B2)
/PS2/MS_CLK_5V: J6.6, U3.11 (B3)
/PS2/MS_DATA_5V: J6.2, U3.10 (B4)
/PSWCLK: J2.1, U7.55 (SWCLK)
/PSWDIO: J2.3, U7.52 (SWDIO)
/PWM_L: R30.2, R31.1, U12.12 (1Y0)
/PWM_R: R28.2, R29.1, U12.1 (2Y0)
/Power/VBUS_IN: C1.1, C2.1, C3.1, R5.2, S6.2, U1.7 (VIN)
/SD1M: R57.1, U5.7 (DM3)
/SD1P: R56.1, U5.8 (DP3)
/SD2M: R59.1, U5.5 (DM2)
/SD2P: R58.1, U5.6 (DP2)
/SHND: JP1.3, R54.2, U10.12 (SHND)
/TDA_L: R38.2, U9.6 (A_LEFT), U12.14 (1Y1)
/TDA_R: R37.1, U9.8 (A_RIGHT), U12.5 (2Y1)
/Tape In/TAPE: C17.2, J9.T
/UDM: J5.5 (DN2), J5.7 (DN1), U4.1 (2Y0)
/UDP: J5.6 (DP1), J5.8 (DP2), U4.12 (1Y0)
/USBSW: R23.2, S2.3, U4.10 (S0)
GND: C1.2, C2.2, C3.2, C6.1, C7.2, C8.2, C9.2, C10.2, C11.2, C12.2, C13.2, C14.2, C15.1, C16.2, C18.2, C19.2, C20.2, C21.2, C22.2, C23.2, C27.1, C28.2, C30.1, C33.1, C34.2, C35.2, C36.1, C37.1, C38.2, C39.2, D1.2 (A), J1.1, J2.2, J3.2, J4.2, J5.1 (GND), J5.12 (GND), J6.3, J7.2 (G_D2), J7.5 (G_D1), J7.8 (G_D0), J7.11 (G_CLK), J7.17 (G_DDC/CEC), J7.20 (SHIELD1), J7.21 (SHIELD2), J7.22 (SHIELD3), J7.23 (SHIELD4), J8.2, J9.S, J12.S, J13.6 (VSS), J14.4 (GND1), J14.8 (GND2), J14.9 (Shield), J15.0, J15.5, J15.6, J15.7, J15.8, J15.10, JP1.6, LD1.1 (K), LD2.1 (K), R6.2, R7.2, R8.2, R9.1, R10.1, R11.1, R12.1, R23.1, R29.2, R31.2, R37.2, R38.1, R39.2, R41.2, R44.1, R52.1, R53.1, R55.1, S1.3, S1.4, S2.4_1 (GND), S2.4_2 (GND), S2.4_3 (GND), S2.4_4 (GND), S3.3, S3.4, S4.2, S4.3 (GND), S5.2, S5.3 (GND), U1.5 (GND), U1.9 (EP), U2.1 (GND), U3.7 (GND), U4.2 (2Y2), U4.4 (2Y3), U4.6 (~E), U4.7 (VEE), U4.8 (GND), U4.9 (S1), U4.11 (1Y3), U4.15 (1Y2), U5.15 (GND), U5.16 (GND), U6.2 (GND), U7.1 (GND), U7.18 (GND), U7.33 (GND), U7.48 (GND), U8.7 (VSS), U8.9 (D14), U8.11 (E), U8.13 (F), U9.4 (AGND), U10.2 (PGND), U10.11 (GND), U10.15 (PGND), U11.4 (V-), U12.2 (2Y2), U12.4 (2Y3), U12.6 (~E), U12.7 (VEE), U12.8 (GND), U12.9 (S1), U12.11 (1Y3), U12.15 (1Y2)
GP25: R24.2, U7.26 (GP25)
unnamed: C4.2, R7.1
unnamed: C17.1, R25.2
unnamed: C19.1, R28.1, R32.2, R35.1
unnamed: C20.1, R30.1, R33.2, R34.1
unnamed: C24.2, R45.2
unnamed: C25.2, R46.2
unnamed: C26.2, R47.2
unnamed: C29.2, R50.2
unnamed: C31.1, R48.1, U11.7
unnamed: C32.1, R49.1, U11.1
unnamed: C5.2, D1.1 (K), L1.1, U1.1 (SW)
unnamed: C14.1, D2.1 (K), J7.18 (+5V)
unnamed: J4.1, S6.3
unnamed: J5.4 (CC1), R9.2
unnamed: J5.10 (CC2), R10.2
unnamed: J5.13 (SHIELD), R12.2
unnamed: J7.12 (CLKN), R17.1
unnamed: J7.10 (CLKP), R21.1
unnamed: J7.9 (D0N), R15.1
unnamed: J7.7 (D0P), R18.1
unnamed: J7.6 (D1N), R19.1
unnamed: J7.4 (D1P), R22.1
unnamed: J7.3 (D2N), R16.1
unnamed: J7.1 (D2P), R20.1
unnamed: J14.3 (D1+), R56.2
unnamed: J14.2 (D1-), R57.2
unnamed: J14.7 (D2+), R58.2
unnamed: J14.6 (D2-), R59.2
unnamed: J15.1, R60.2, R63.2
unnamed: J15.2, R61.2, R64.2
unnamed: J15.3, R62.2, R65.2
unnamed: J15.13, R66.1
unnamed: J15.14, R67.1
unnamed: LD1.2 (A), R14.1
unnamed: LD2.2 (A), R24.1
unnamed: C5.1, U1.8 (BST)
unnamed: C4.1, U1.3 (COMP)
unnamed: R5.1, R6.1, U1.2 (EN)
unnamed: R11.2, R13.2, U1.4 (FB)
unnamed: R8.1, U1.6 (FREQ)
unnamed: U5.12 (VD33), U5.14 (VD3)
unnamed: R25.1, R26.2, U8.1 (A)
unnamed: R27.1, U8.3 (B)
unnamed: U8.4 (H=*B), U8.5 (C)
unnamed: R26.1, R27.2, U8.2 (G-*A)
unnamed: C23.1, U9.7 (FLT)
unnamed: C21.1, C22.1, R36.1, U9.5 (VA)
unnamed: R45.1, U10.7 (INL)
unnamed: R50.1, U10.10 (INR)
unnamed: C28.1, U10.8 (VREF)
unnamed: C27.2, R43.1, R44.2, U11.3 (+), U11.5 (+)
unnamed: R47.1, R49.2, U11.2 (-)
unnamed: R46.1, R48.2, U11.6 (-)
unnamed: C30.2, C33.2, R43.2, R51.2, U11.8 (V+)
VBUS: C6.2, C7.1, C8.1, C10.1, C13.1, C15.2, C16.1, C34.1, C35.1, C36.2, C38.1, C39.1, D2.2 (A), J3.3, J5.2 (VBUS), J5.11 (VBUS), J6.4, J8.1, J14.1 (VBUS1), J14.5 (VBUS2), JP1.8, L1.2, R13.1, R36.2, R51.1, R54.1, S2.2, U2.3 (VI), U3.14 (VCCB), U4.16 (VCC), U5.13 (VDD5), U7.60 (VBUS), U10.4 (PVDD), U10.5 (MUTE), U10.6 (VDD), U10.13 (PVDD), U12.16 (VCC)
